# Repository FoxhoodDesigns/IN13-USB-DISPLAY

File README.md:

# IN13 USB Display
Designed as a companion to the Mini-Hardware-Monitor project ( https://github.com/FoxhoodDesigns/Mini-Hardware-Monitor ), a testbed for KiCad 9.0's new features and as a Evaluation project for the newer Microchip AVR DU Microcontrollers with USB interface

This project provides a trio of old Soviet-Era IN-13 Nixie Bargraphs that can be controlled via USB CDC communication. Both as an External display OR as a Internal display (case-mod).
The board is divided into 3 parts. 
+ The boost converter that provides ~180V to ignite the IN13 tubes
+ a set of three Voltage-controlled Current sinks to manipulate the strength of the signal to the tube based on the duty cycle of a PWM input
+ A AVR64DU32 Microcontroller handling USB-communication, PWM output and potential Sensor interface via QWIIC/STEMMA-QT interface.

# Current Status
Figuring out how to set the AVR64DU as CDC USB device via Microchip MCC kit. Once done the PCB's can be sent out.

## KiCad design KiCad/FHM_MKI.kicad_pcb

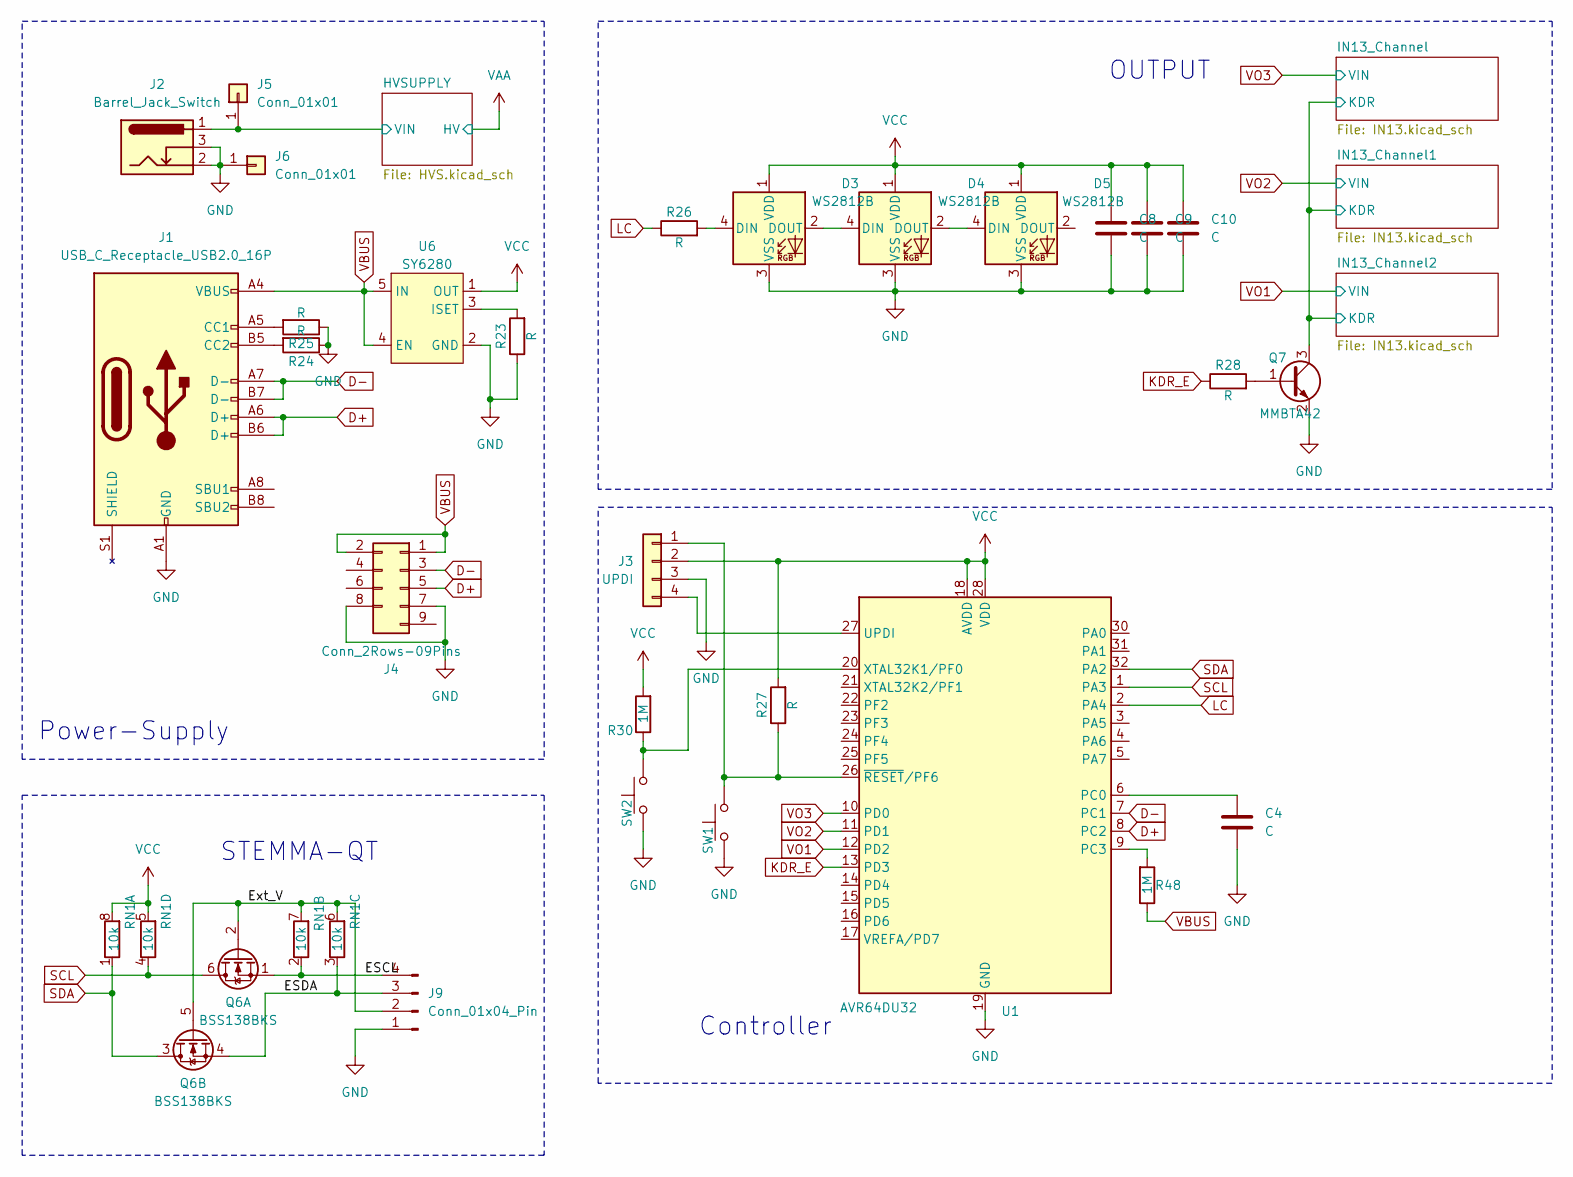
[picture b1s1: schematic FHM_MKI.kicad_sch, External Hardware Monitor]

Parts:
C4, C8, C9, C10: C; C_0805_2012Metric
D3, D4, D5: WS2812B; LED_WS2812B_PLCC4_5.0x5.0mm_P3.2mm
J1: USB_C_Receptacle_USB2.0_16P; USB_C_Receptacle_UJ20-C-V-C-3-SMT-TR_TopMnt_Vertical
J2: Barrel_Jack_Switch; BarrelJack_CUI_PJ-006A_Vertical
J3: UPDI; PinHeader_1x04_P2.54mm_Vertical_SMD_Pin1Left
J4: Conn_2Rows-09Pins; PinHeader_2x05_P2.54mm_Vertical_SMD
J5, J6: Conn_01x01; SolderWirePad_1x01_SMD_1x2mm
J9: Conn_01x04_Pin; JST_SH_BM04B-SRSS-TB_1x04-1MP_P1.00mm_Vertical
Q6: BSS138BKS; SOT-363_SC-70-6_Handsoldering
Q7: MMBTA42; SOT-23
R23, R24, R25, R26, R27, R28: R; R_0805_2012Metric
R30, R48: 1M; R_0805_2012Metric_Pad1.20x1.40mm_HandSolder
RN1: 10k; R_Array_Convex_4x0603
SW1, SW2: PTH_RA_7.4x4.3mm; SW_Push_1P1T_NO_Vertical_Wuerth_434133025816
U1: AVR64DU32; TQFP-32_7x7mm_P0.8mm
U6: SY6280; SOT-23-5_HandSoldering

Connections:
/ESCL: J9.4, Q6.1 (S), RN1.2 (R2.1)
/ESDA: J9.3, Q6.4 (S), RN1.3 (R3.1)
/Ext_V: J9.2, Q6.2 (G), Q6.5 (G), RN1.6 (R3.2), RN1.7 (R2.2)
/HVSUPPLY/VIN: J2.1, J5.1; also elsewhere on the board
/IN13_Channel/KDR: Q7.3 (C); also elsewhere on the board
D+: J1.A6 (D+), J1.B6 (D+), J4.5, U1.8 (PC2)
D-: J1.A7 (D-), J1.B7 (D-), J4.3, U1.7 (PC1)
GND: C4.2, C8.2, C9.2, C10.2, D3.3 (VSS), D4.3 (VSS), D5.3 (VSS), J1.A1 (GND), J1.A12 (GND), J1.B1 (GND), J1.B12 (GND), J2.2, J2.3, J3.3, J4.7, J4.8, J6.1, J9.1, Q7.2 (E), R23.1, R24.1, R25.1, SW1.1, SW2.1, U1.19 (GND), U1.29 (GND), U6.2 (GND); also elsewhere on the board
KDR_E: R28.1, U1.13 (PD3)
LC: R26.1, U1.2 (PA4)
unnamed: D3.4 (DIN), R26.2
unnamed: D3.2 (DOUT), D4.4 (DIN)
unnamed: D4.2 (DOUT), D5.4 (DIN)
unnamed: J1.A5 (CC1), R25.2
unnamed: J1.B5 (CC2), R24.2
unnamed: J3.1, R27.1, SW1.2, U1.26 (~RESET/PF6)
unnamed: J3.4, U1.27 (UPDI)
unnamed: Q7.1 (B), R28.2
unnamed: C4.1, U1.6 (PC0)
unnamed: R48.2, U1.9 (PC3)
unnamed: R30.1, SW2.2, U1.20 (XTAL32K1/PF0)
unnamed: R23.2, U6.3 (ISET)
SCL: Q6.6 (D), RN1.4 (R4.1), U1.1 (PA3)
SDA: Q6.3 (D), RN1.1 (R1.1), U1.32 (PA2)
VBUS: J1.A4 (VBUS), J1.A9 (VBUS), J1.B4 (VBUS), J1.B9 (VBUS), J4.1, J4.2, R48.1, U6.4 (EN), U6.5 (IN)
VCC: C8.1, C9.1, C10.1, D3.1 (VDD), D4.1 (VDD), D5.1 (VDD), J3.2, R27.2, R30.2, RN1.5 (R4.2), RN1.8 (R1.2), U1.18 (AVDD), U1.28 (VDD), U6.1 (OUT); also elsewhere on the board
VO1: U1.12 (PD2); also elsewhere on the board
VO2: U1.11 (PD1); also elsewhere on the board
VO3: U1.10 (PD0); also elsewhere on the board

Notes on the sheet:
Controller
Power-Supply
STEMMA-QT
OUTPUT

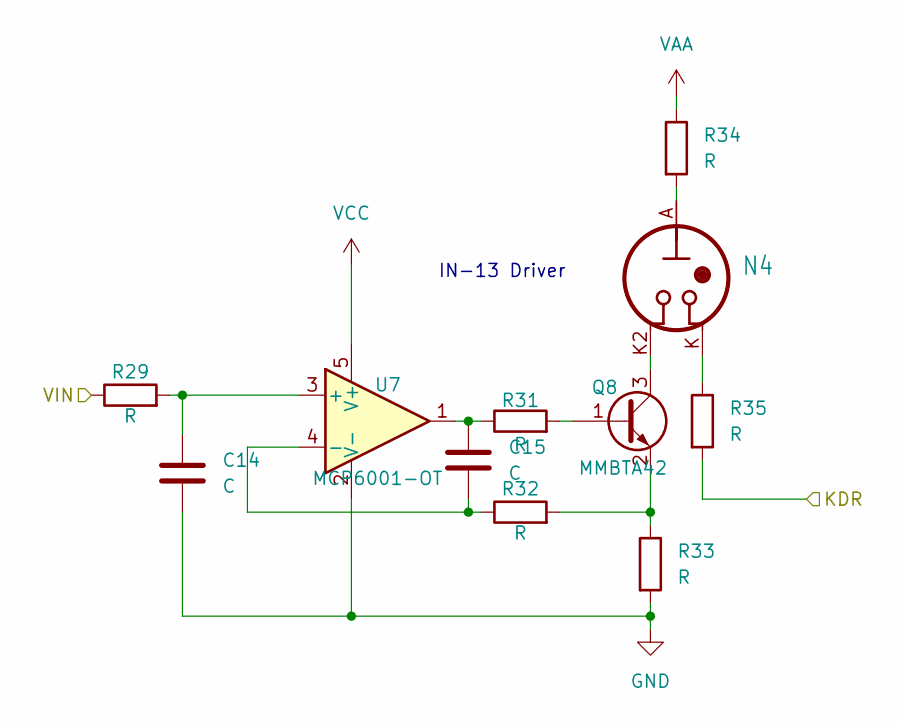
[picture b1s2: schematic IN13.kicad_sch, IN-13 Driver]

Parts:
C14, C15: C; C_0805_2012Metric
N4: IN-13
Q8: MMBTA42; SOT-23
R29, R31, R32: R; R_0805_2012Metric
R33, R35: R; R_0805_2012Metric_Pad1.20x1.40mm_HandSolder
R34: R; R_2512_6332Metric_Pad1.40x3.35mm_HandSolder
U7: MCP6001-OT; SOT-23-5

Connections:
/IN13_Channel/KDR: R35.2; also elsewhere on the board
GND: C14.2, R33.2, U7.2 (V-); also elsewhere on the board
unnamed: C15.1, R31.1, U7.1
unnamed: N4.A, R34.2
unnamed: N4.K, R35.1
unnamed: Q8.1 (B), R31.2
unnamed: N4.K2, Q8.3 (C)
unnamed: Q8.2 (E), R32.2, R33.1
unnamed: C14.1, R29.2, U7.3 (+)
unnamed: C15.2, R32.1, U7.4 (-)
VAA: R34.1; also elsewhere on the board
VCC: U7.5 (V+); also elsewhere on the board
VO3: R29.1; also elsewhere on the board

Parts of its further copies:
C16, C17, C18, C19: C; C_0805_2012Metric
N5, N6: IN-13
Q9, Q10: MMBTA42; SOT-23
R36, R37, R38, R42, R43, R44: R; R_0805_2012Metric
R39, R41, R45, R47: R; R_0805_2012Metric_Pad1.20x1.40mm_HandSolder
R40, R46: R; R_2512_6332Metric_Pad1.40x3.35mm_HandSolder
U8, U9: MCP6001-OT; SOT-23-5

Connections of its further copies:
/IN13_Channel/KDR: R41.2, R47.2; also elsewhere on the board
GND: C16.2, C18.2, R39.2, R45.2, U8.2 (V-), U9.2 (V-); also elsewhere on the board
unnamed: C17.1, R37.1, U8.1
unnamed: C19.1, R43.1, U9.1
unnamed: N5.A, R40.2
unnamed: N5.K, R41.1
unnamed: N6.A, R46.2
unnamed: N6.K, R47.1
unnamed: Q9.1 (B), R37.2
unnamed: N5.K2, Q9.3 (C)
unnamed: Q9.2 (E), R38.2, R39.1
unnamed: Q10.1 (B), R43.2
unnamed: N6.K2, Q10.3 (C)
unnamed: Q10.2 (E), R44.2, R45.1
unnamed: C16.1, R36.2, U8.3 (+)
unnamed: C17.2, R38.1, U8.4 (-)
unnamed: C18.1, R42.2, U9.3 (+)
unnamed: C19.2, R44.1, U9.4 (-)
VAA: R40.1, R46.1; also elsewhere on the board
VCC: U8.5 (V+), U9.5 (V+); also elsewhere on the board
VO1: R42.1; also elsewhere on the board
VO2: R36.1; also elsewhere on the board

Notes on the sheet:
IN-13 Driver

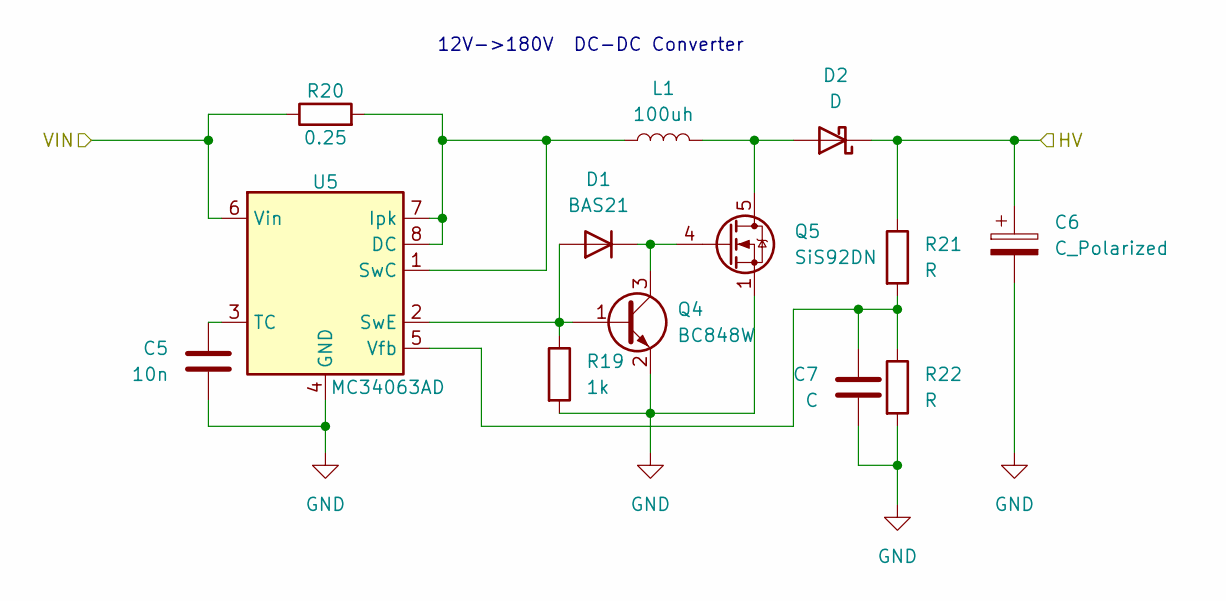
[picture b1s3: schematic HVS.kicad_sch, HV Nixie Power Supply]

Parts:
C5: 10n; C_0805_2012Metric
C6: C_Polarized; CP_Elec_8x11.9
C7: C; C_0805_2012Metric
D1: BAS21; SOT-23
D2: D; D_SMA
L1: 100uh; L_12x12mm_H8mm
Q4: BC848W; SOT-323_SC-70
Q5: SiS92DN; Vishay_PowerPAK_1212-8_Single
R19: 1k; C_0805_2012Metric_Pad1.18x1.45mm_HandSolder
R20: 0.25; R_2512_6332Metric_Pad1.40x3.35mm_HandSolder
R21, R22: R; C_0805_2012Metric_Pad1.18x1.45mm_HandSolder
U5: MC34063AD; SOIC-8_3.9x4.9mm_P1.27mm

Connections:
/HVSUPPLY/VIN: R20.1, U5.6 (Vin); also elsewhere on the board
GND: C5.2, C6.2, C7.2, Q4.2 (E), Q5.1 (S), Q5.2 (S), Q5.3 (S), R19.2, R22.2, U5.4 (GND); also elsewhere on the board
unnamed: D1.1 (A), Q4.1 (B), R19.1, U5.2 (SwE)
unnamed: D1.3 (K), Q4.3 (C), Q5.4 (G)
unnamed: D2.2 (A), L1.2, Q5.5 (D)
unnamed: L1.1, R20.2, U5.1 (SwC), U5.7 (Ipk), U5.8 (DC)
unnamed: C5.1, U5.3 (TC)
unnamed: C7.1, R21.2, R22.1, U5.5 (Vfb)
VAA: C6.1, D2.1 (K), R21.1; also elsewhere on the board

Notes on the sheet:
12V->180V DC-DC Converter

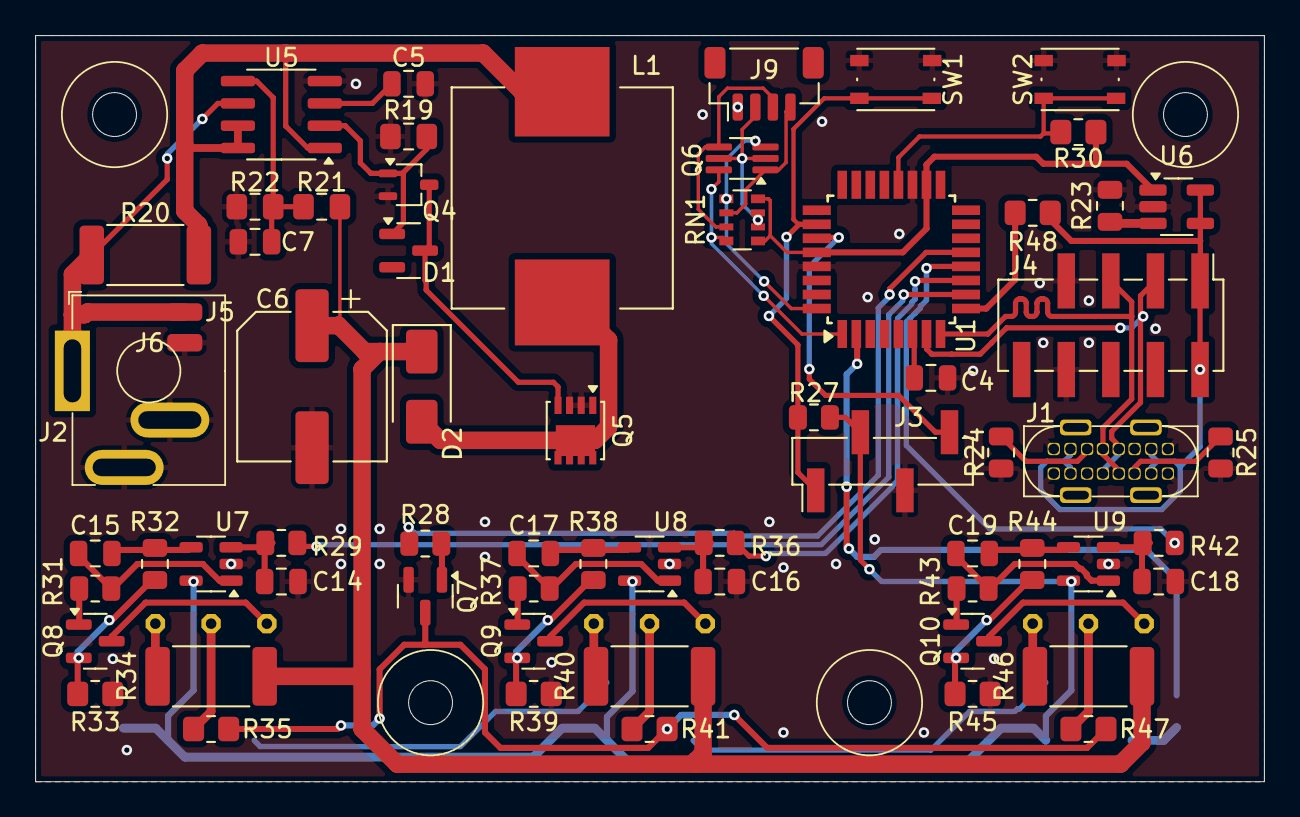
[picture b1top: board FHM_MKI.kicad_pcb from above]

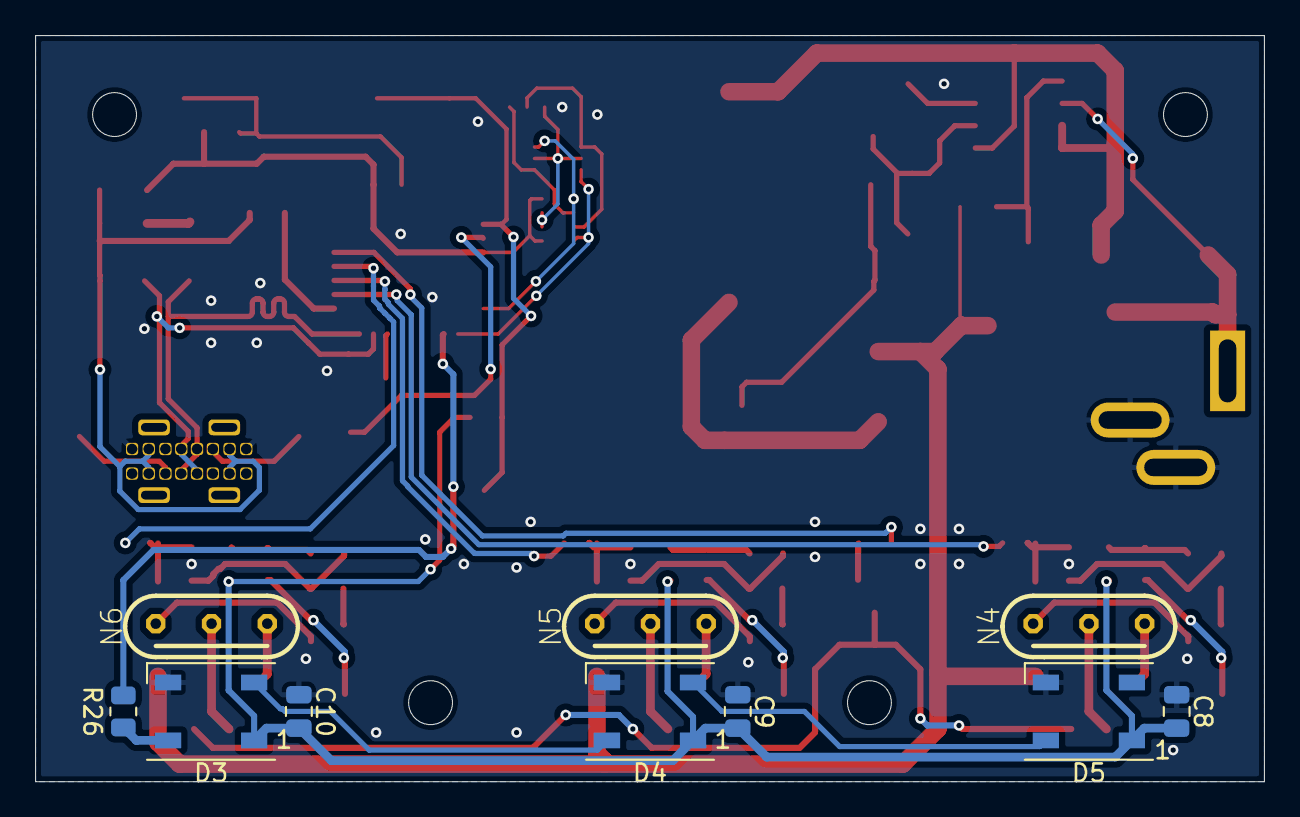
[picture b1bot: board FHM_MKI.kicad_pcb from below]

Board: 2 copper layers, 70.0 x 42.5 mm, 75 parts (10 on the bottom side), 60 nets.

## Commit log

2025-02-23 Initial Upload
